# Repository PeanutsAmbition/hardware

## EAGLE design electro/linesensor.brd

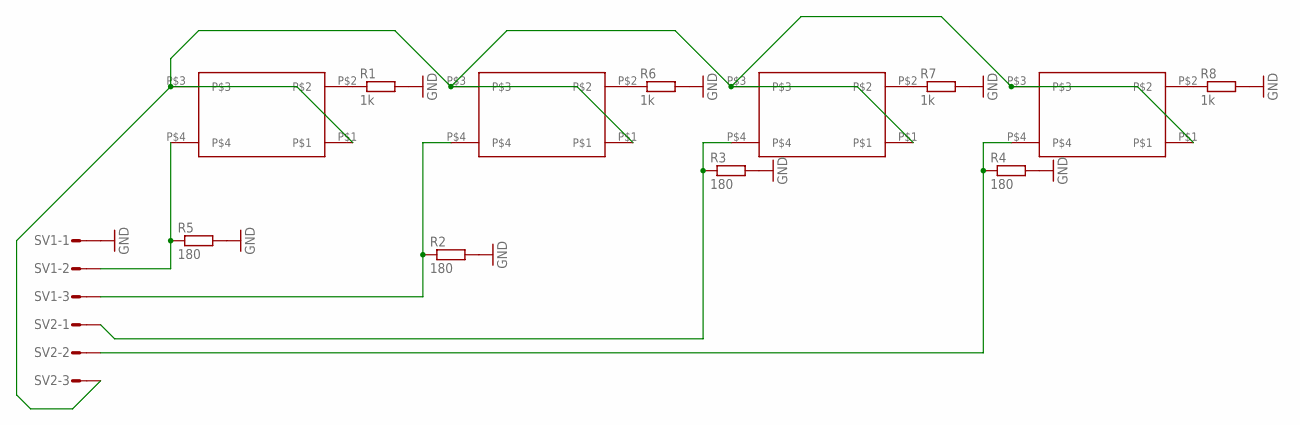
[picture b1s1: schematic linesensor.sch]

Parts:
R1, R6, R7, R8: 1k; 0204V
R2, R3, R4, R5: 180; 0204V
SV1, SV2: S03P
U$1, U$2, U$3, U$4: TPR105F

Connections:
GND: R1.2, R2.2, R3.2, R4.2, R5.2, R6.2, R7.2, R8.2, SV1.1
unnamed: SV2.3, U$1.P$1, U$1.P$3, U$2.P$1, U$2.P$3, U$3.P$1, U$3.P$3, U$4.P$1, U$4.P$3
unnamed: R2.1, SV1.3, U$2.P$4
unnamed: R3.1, SV2.1, U$3.P$4
unnamed: R4.1, SV2.2, U$4.P$4
unnamed: R1.1, U$1.P$2
unnamed: R6.1, U$2.P$2
unnamed: R5.1, SV1.2, U$1.P$4
unnamed: R7.1, U$3.P$2
unnamed: R8.1, U$4.P$2

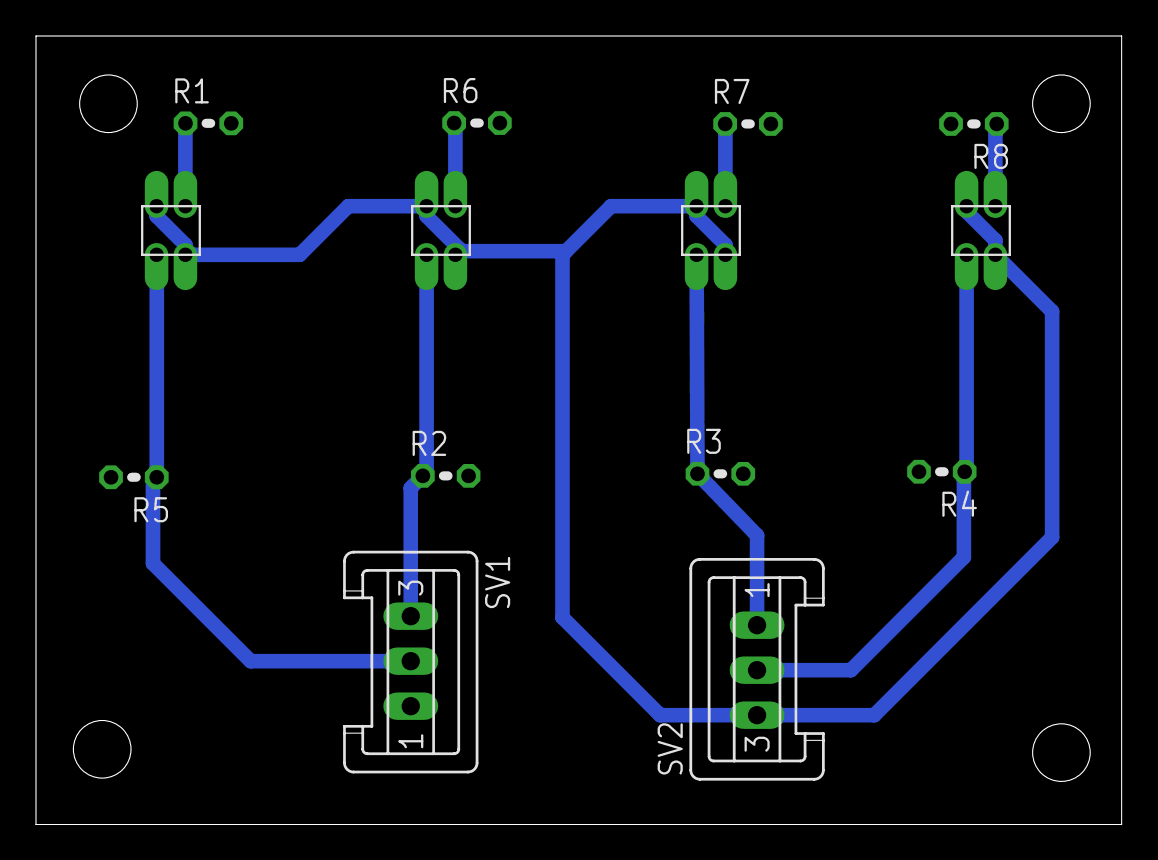
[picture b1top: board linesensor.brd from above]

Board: 2 copper layers, 60.3 x 43.8 mm, 14 parts (0 on the bottom side), 10 nets.

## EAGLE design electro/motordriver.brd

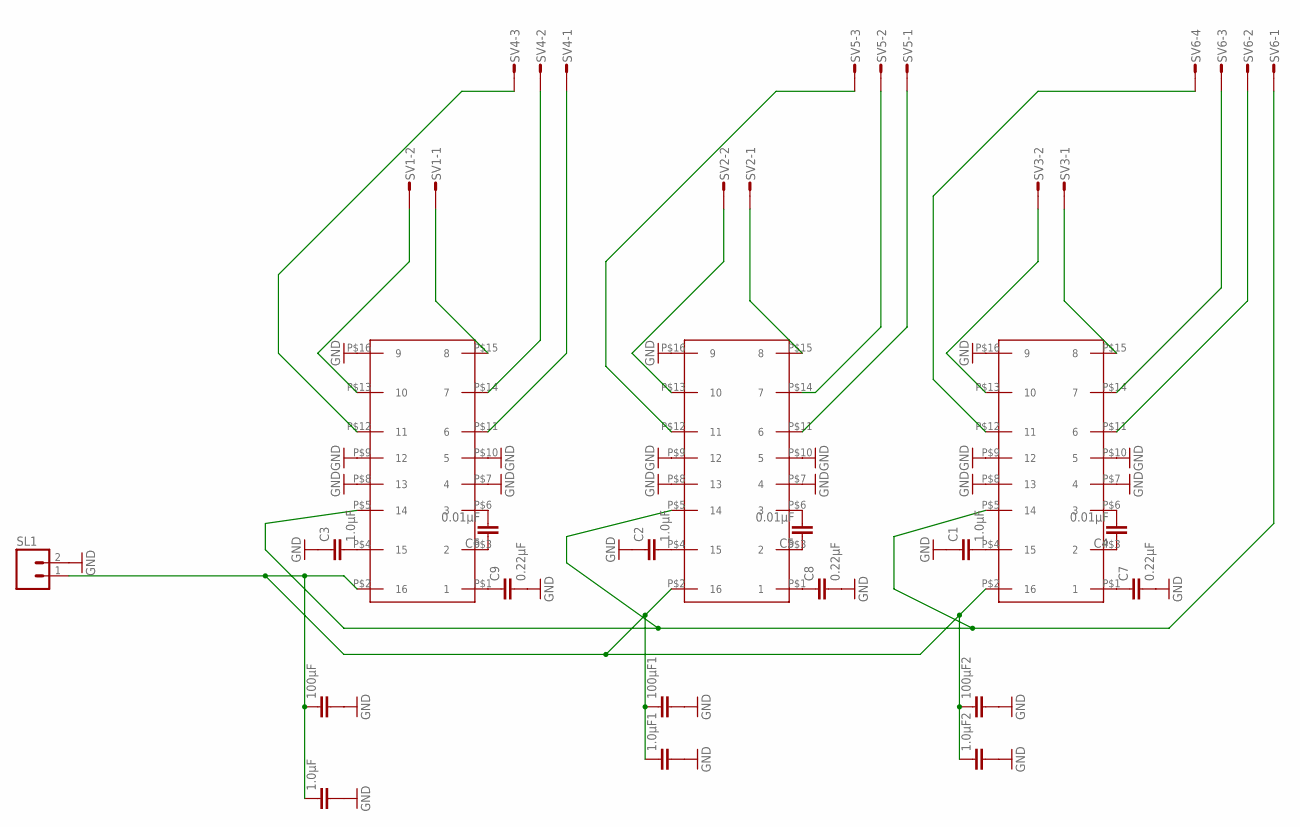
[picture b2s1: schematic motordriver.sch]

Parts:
1.0μF, 1.0μF1, 1.0μF2, 100μF, 100μF1, 100μF2: C-EU025-024X044; C025-024X044
C1, C2, C3: 1.0μF; C025-024X044
C4, C5, C6: 0.01μF; C025-024X044
C7, C8, C9: 0.22μF; C025-024X044
SL1: M02; 02P
SV1, SV2, SV3: L02P
SV4, SV5: S03P
SV6: S04P
U$1, U$2, U$3: TB6549PG

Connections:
GND: 1.0μF.2, 1.0μF1.2, 1.0μF2.2, 100μF.2, 100μF1.2, 100μF2.2, C1.1, C2.1, C3.1, C7.2, C8.2, C9.2, SL1.2, U$1.P$7 (4), U$1.P$8 (13), U$1.P$9 (12), U$1.P$10 (5), U$1.P$16 (9), U$2.P$7 (4), U$2.P$8 (13), U$2.P$9 (12), U$2.P$10 (5), U$2.P$16 (9), U$3.P$7 (4), U$3.P$8 (13), U$3.P$9 (12), U$3.P$10 (5), U$3.P$16 (9)
unnamed: SV1.2, U$1.P$13 (10)
unnamed: SV1.1, U$1.P$15 (8)
unnamed: SV2.2, U$2.P$13 (10)
unnamed: SV2.1, U$2.P$15 (8)
unnamed: SV3.2, U$3.P$13 (10)
unnamed: SV3.1, U$3.P$15 (8)
unnamed: SV4.3, U$1.P$12 (11)
unnamed: SV5.3, U$2.P$12 (11)
unnamed: C1.2, U$3.P$4 (15)
unnamed: SV4.2, U$1.P$14 (7)
unnamed: SV4.1, U$1.P$11 (6)
unnamed: SV5.2, U$2.P$14 (7)
unnamed: SV5.1, U$2.P$11 (6)
unnamed: SV6.3, U$3.P$14 (7)
unnamed: SV6.2, U$3.P$11 (6)
unnamed: SV6.1, U$1.P$5 (14), U$2.P$5 (14), U$3.P$5 (14)
unnamed: C2.2, U$2.P$4 (15)
unnamed: C3.2, U$1.P$4 (15)
unnamed: C4.1, U$3.P$3 (2)
unnamed: C4.2, U$3.P$6 (3)
unnamed: C5.1, U$2.P$3 (2)
unnamed: C5.2, U$2.P$6 (3)
unnamed: C6.1, U$1.P$3 (2)
unnamed: C6.2, U$1.P$6 (3)
unnamed: C7.1, U$3.P$1 (1)
unnamed: C8.1, U$2.P$1 (1)
unnamed: C9.1, U$1.P$1 (1)
unnamed: SV6.4, U$3.P$12 (11)
unnamed: 1.0μF.1, 1.0μF1.1, 1.0μF2.1, 100μF.1, 100μF1.1, 100μF2.1, SL1.1, U$1.P$2 (16), U$2.P$2 (16), U$3.P$2 (16)

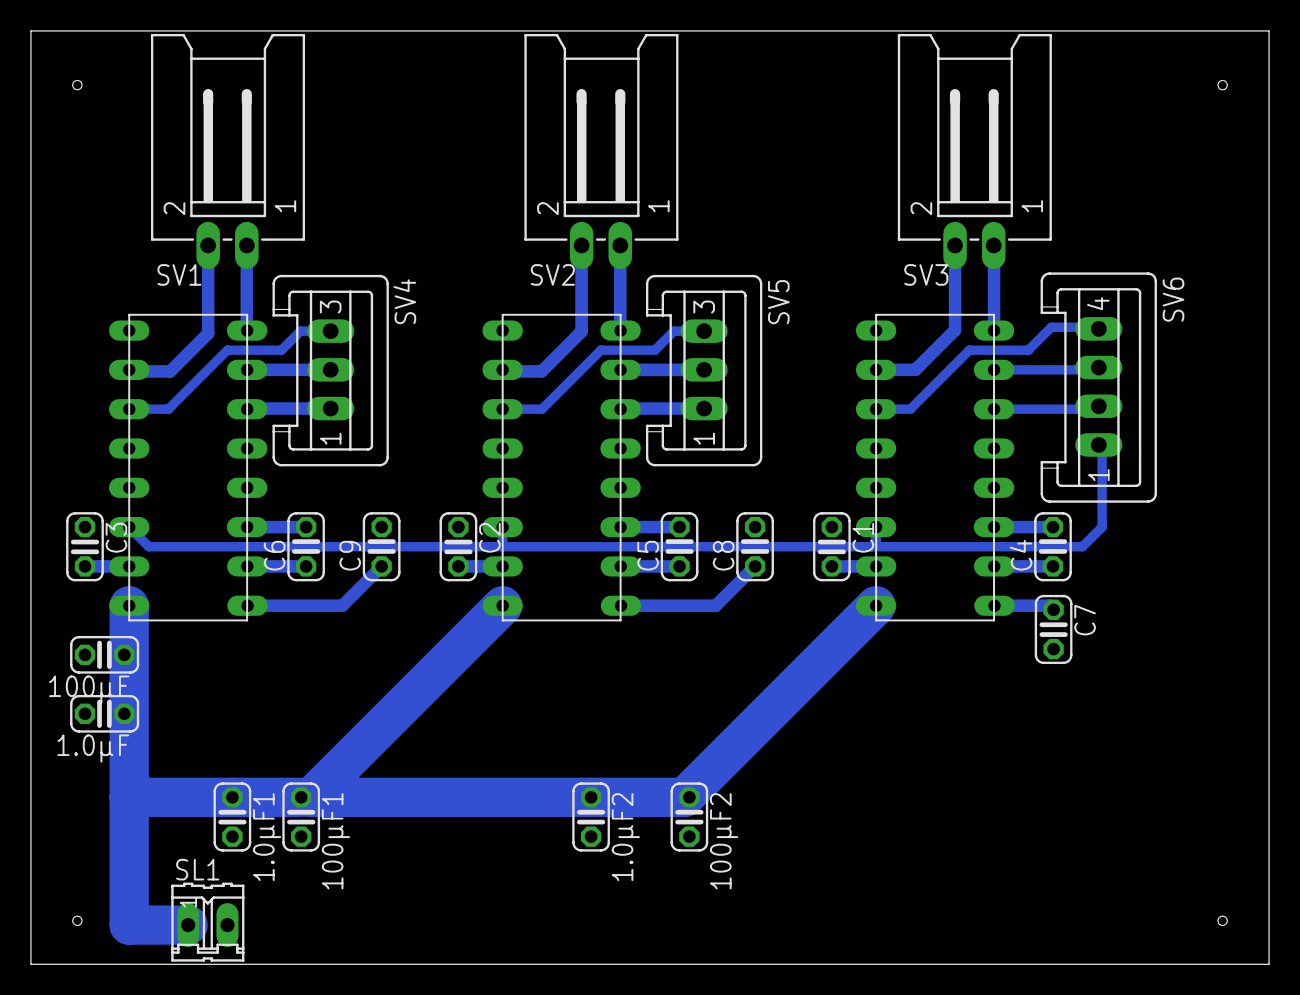
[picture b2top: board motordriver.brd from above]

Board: 2 copper layers, 80.0 x 60.3 mm, 25 parts (0 on the bottom side), 30 nets.

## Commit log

2014-11-29 回路データ追加
2014-12-05 大砲
    知能ロボコンに載せる大砲のCAD図です。
    最新は知能ロボコン発射筒1.1.iamです。
